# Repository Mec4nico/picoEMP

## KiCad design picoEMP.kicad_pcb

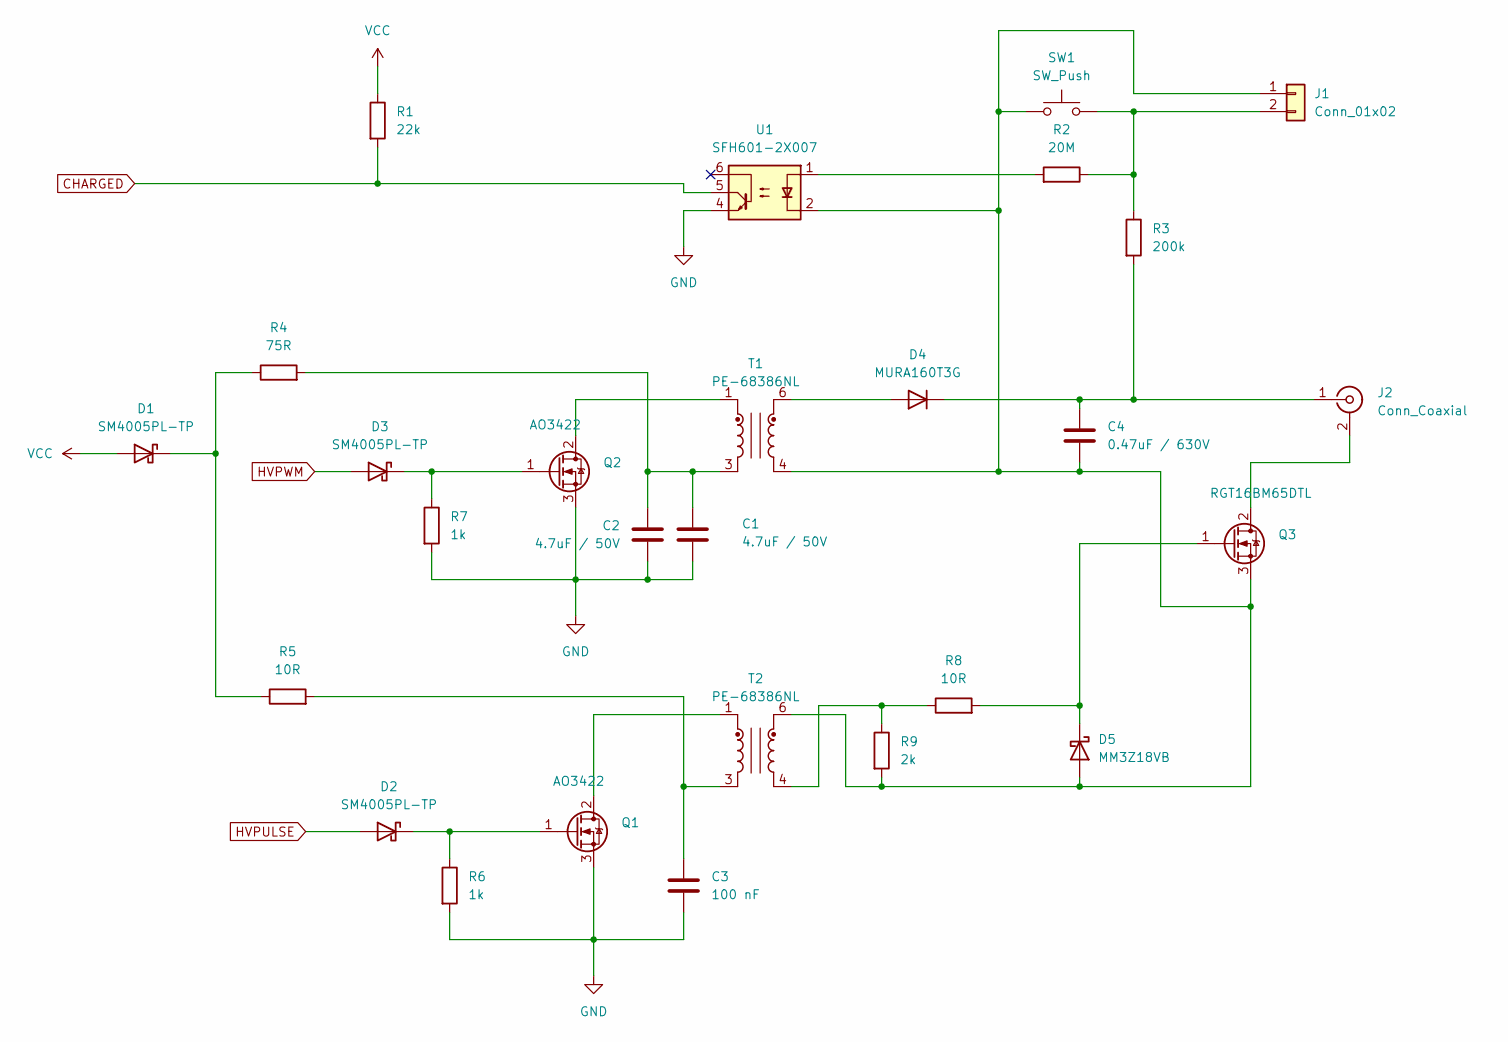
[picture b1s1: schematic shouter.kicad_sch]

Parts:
C1, C2: 4.7uF / 50V; C_1206_3216Metric; PART_NUMBER_LCSC C51205
C3: 100 nF; C_1206_3216Metric; PART_NUMBER_LCSC C24497
C4: 0.47uF / 630V; C_1812_4532Metric; PART_NUMBER_LCSC C106147
D1, D2, D3: SM4005PL-TP; Nexperia_CFP3_SOD-123W; PART_NUMBER_LCSC C330237
D4: MURA160T3G; D_1812_4532Metric; PART_NUMBER_LCSC C50432
D5: MM3Z18VB; Nexperia_CFP3_SOD-123W; PART_NUMBER_LCSC C891584
J1: Conn_01x02; PinHeader_1x02_P2.54mm_Vertical
J2: Conn_Coaxial; SMA_Amphenol_132289_EdgeMount
Q1, Q2: AO3422; SOT-23; PART_NUMBER_LCSC C37130
Q3: RGT16BM65DTL; TO-252-2; PART_NUMBER_LCSC C3193927
R1: 22k; R_1206_3216Metric; PART_NUMBER_LCSC C1409
R2: 20M; R_1206_3216Metric; PART_NUMBER_LCSC C71198
R3: 200k; R_1206_3216Metric; PART_NUMBER_LCSC C17954
R4: 75R; R_1206_3216Metric; PART_NUMBER_LCSC C17954
R5, R8: 10R; R_1206_3216Metric; PART_NUMBER_LCSC C17903
R6, R7: 1k; R_1206_3216Metric; PART_NUMBER_LCSC C4410
R9: 2k; R_1206_3216Metric; PART_NUMBER_LCSC C17944
SW1: SW_Push; SW_SPST_CK_RS282G05A3; PART_NUMBER_LCSC C318938
T1, T2: PE-68386NL; Pulse_PA2001NL; PART_NUMBER_LCSC C581397
U1: SFH601-2X007; SMDIP-6_W7.62mm; PART_NUMBER_LCSC C17237090

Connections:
CHARGED: R1.2, U1.5; also elsewhere on the board
GND: C1.2, C2.2, C3.2, Q1.3 (S), Q2.3 (S), R6.2, R7.2, U1.4; also elsewhere on the board
HVPULSE: D2.2 (A); also elsewhere on the board
HVPWM: D3.2 (A); also elsewhere on the board
unnamed: C1.1, C2.1, R4.2, T1.3
unnamed: C3.1, R5.2, T2.3
unnamed: D1.1 (K), R4.1, R5.1
unnamed: D2.1 (K), Q1.1 (G), R6.1
unnamed: D3.1 (K), Q2.1 (G), R7.1
unnamed: D4.2 (A), T1.6
unnamed: C4.1, D4.1 (K), J2.1 (In), R3.2
unnamed: C4.2, D5.2 (A), J1.1, Q3.3 (S), R9.2, SW1.1, T1.4, T2.6, U1.2
unnamed: D5.1 (K), Q3.1 (G), R8.2
unnamed: J2.2 (Ext), Q3.2 (D)
unnamed: Q1.2 (D), T2.1
unnamed: Q2.2 (D), T1.1
unnamed: R8.1, R9.1, T2.4
VCC: D1.2 (A), R1.1; also elsewhere on the board

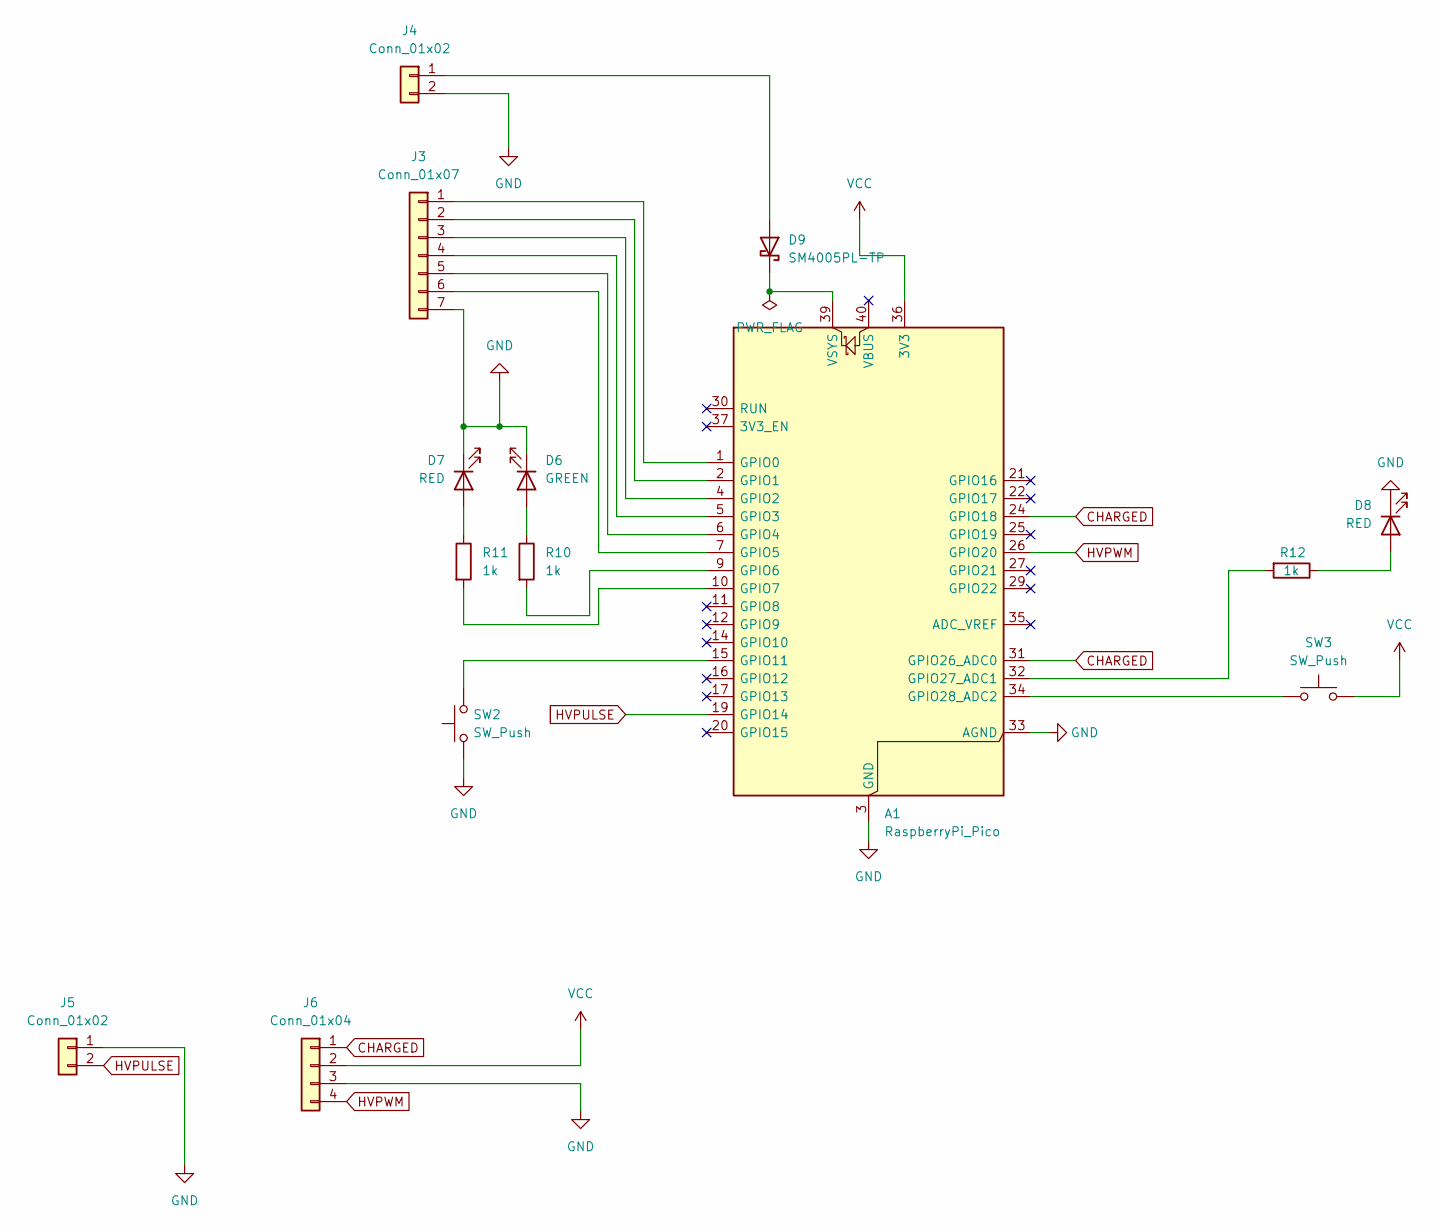
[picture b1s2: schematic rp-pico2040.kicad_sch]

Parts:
A1: RaspberryPi_Pico; RaspberryPi_Pico_Common_Unspecified
D6: GREEN; LED_1206_3216Metric; PART_NUMBER_LCSC C3646937
D7: RED; LED_1206_3216Metric; PART_NUMBER_LCSC C434444
D8: RED; LED_1206_3216Metric; PART_NUMBER_LCSC C3646938
D9: SM4005PL-TP; Nexperia_CFP3_SOD-123W; PART_NUMBER_LCSC C330237
J3: Conn_01x07; PinHeader_1x07_P2.54mm_Vertical
J4, J5: Conn_01x02; PinHeader_1x02_P2.54mm_Vertical
J6: Conn_01x04; PinHeader_1x04_P2.54mm_Vertical
R10, R11, R12: 1k; R_1206_3216Metric; PART_NUMBER_LCSC C4410
SW2, SW3: SW_Push; SW_SPST_CK_RS282G05A3; PART_NUMBER_LCSC C318938

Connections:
CHARGED: A1.24 (GPIO18), A1.31 (GPIO26_ADC0), J6.1; also elsewhere on the board
GND: A1.3 (GND), A1.8 (GND), A1.13 (GND), A1.18 (GND), A1.23 (GND), A1.28 (GND), A1.33 (AGND), A1.38 (GND), D6.1 (K), D7.1 (K), D8.1 (K), J3.7, J4.2, J5.1, J6.3, SW2.1; also elsewhere on the board
HVPULSE: A1.19 (GPIO14), J5.2; also elsewhere on the board
HVPWM: A1.26 (GPIO20), J6.4; also elsewhere on the board
unnamed: A1.1 (GPIO0), J3.1
unnamed: A1.2 (GPIO1), J3.2
unnamed: A1.4 (GPIO2), J3.3
unnamed: A1.5 (GPIO3), J3.4
unnamed: A1.6 (GPIO4), J3.5
unnamed: A1.7 (GPIO5), J3.6
unnamed: A1.9 (GPIO6), R10.2
unnamed: A1.10 (GPIO7), R11.2
unnamed: A1.15 (GPIO11), SW2.2
unnamed: A1.32 (GPIO27_ADC1), R12.2
unnamed: A1.34 (GPIO28_ADC2), SW3.1
unnamed: A1.39 (VSYS), D9.1 (K)
unnamed: D6.2 (A), R10.1
unnamed: D7.2 (A), R11.1
unnamed: D8.2 (A), R12.1
unnamed: D9.2 (A), J4.1
VCC: A1.36 (3V3), J6.2, SW3.2; also elsewhere on the board

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
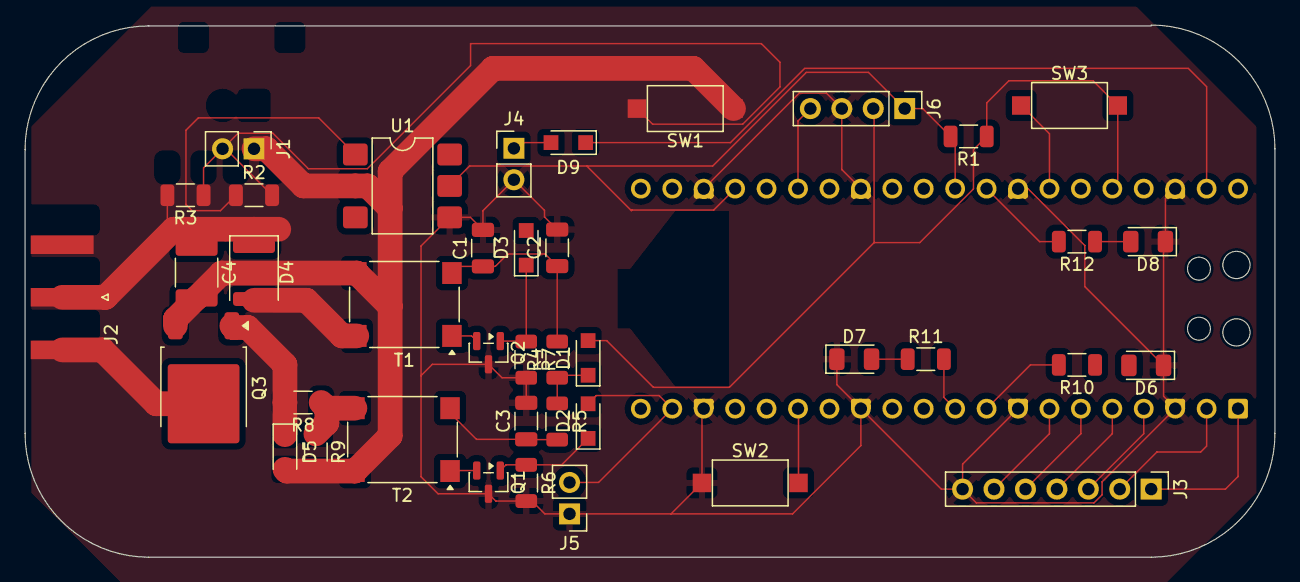
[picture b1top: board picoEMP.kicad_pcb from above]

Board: 2 copper layers, 101.0 x 43.0 mm, 41 parts (1 on the bottom side), 36 nets.

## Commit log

2025-12-08 addede schematic components
2025-12-08 added excluded previous files
2025-12-09 net finished, pending add shouter components any footprint
2025-12-13 update components, pending route signals of connectors
2026-03-18 update components and footprints
2026-03-19 'pads_añadidos'
